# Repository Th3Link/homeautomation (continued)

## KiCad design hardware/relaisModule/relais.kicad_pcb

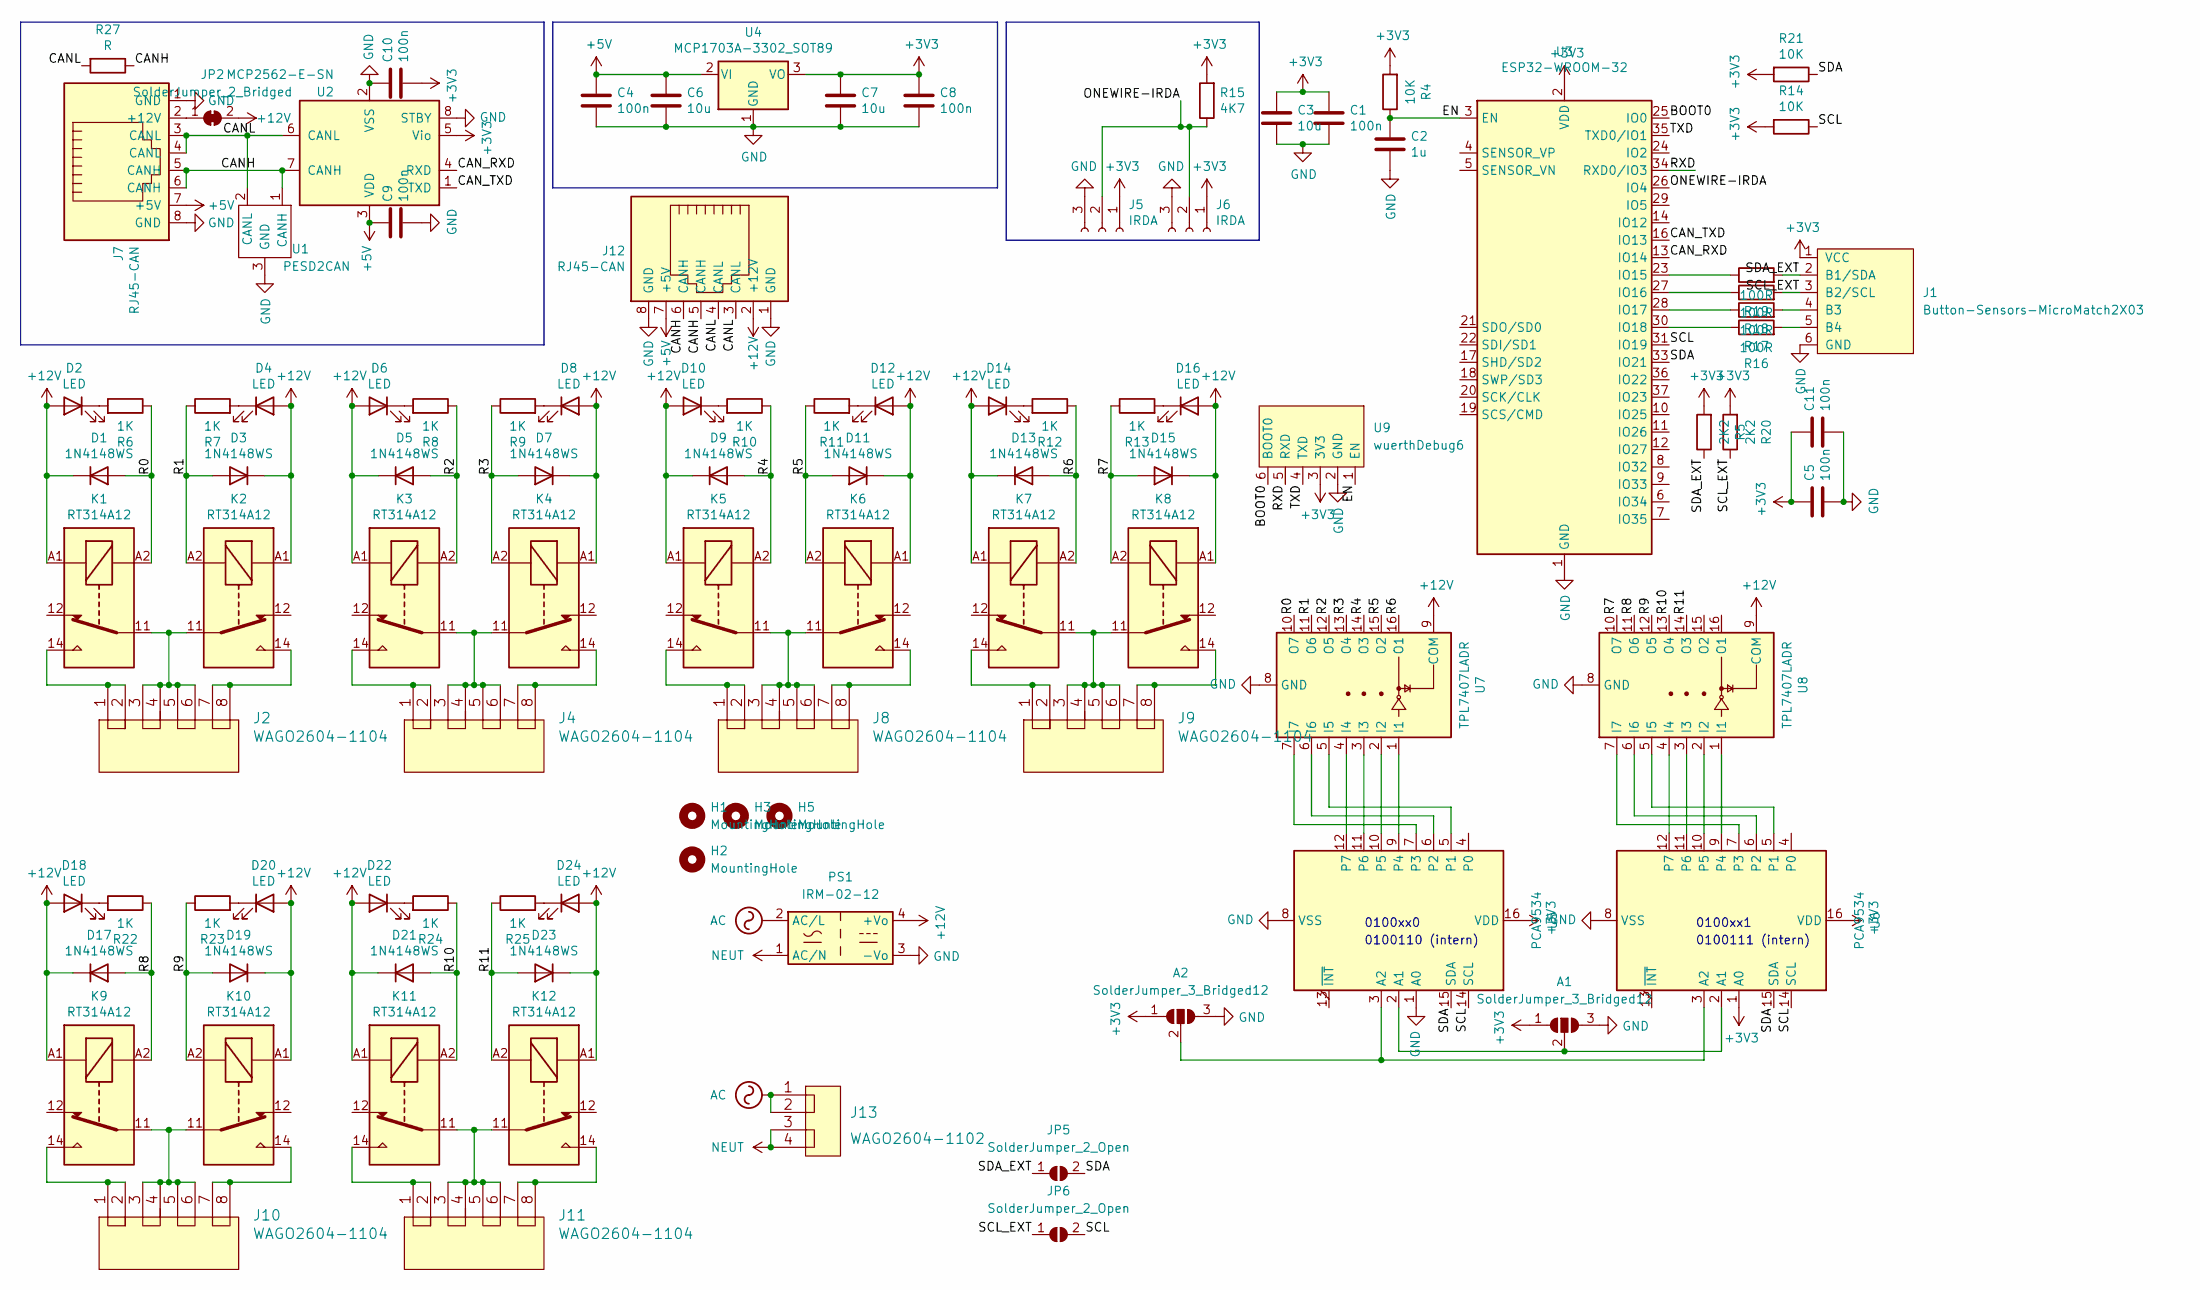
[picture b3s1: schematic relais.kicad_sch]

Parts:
A1, A2: SolderJumper_3_Bridged12; SolderJumper-3_P1.3mm_Open_RoundedPad1.0x1.5mm
C1, C4, C5, C8, C9, C10, C11: 100n; C_0603_1608Metric_Pad1.08x0.95mm_HandSolder
C2: 1u; C_0603_1608Metric_Pad1.08x0.95mm_HandSolder
C3, C6, C7: 10u; C_0805_2012Metric_Pad1.18x1.45mm_HandSolder
D1, D3, D5, D7, D9, D11, D13, D15, D17, D19, D21, D23: 1N4148WS; D_SOD-123
D2, D4, D6, D8, D10, D12, D14, D16, D18, D20, D22, D24: LED; LED_0603_1608Metric_Pad1.05x0.95mm_HandSolder
H1, H2, H3, H5: MountingHole; MountingHole_3.2mm_M3_DIN965
J1: Button-Sensors-MicroMatch2X03; 02x03MicroMatch
J2, J4, J8, J9, J10, J11: WAGO2604-1104
J5, J6: IRDA; PinHeader_1x03_P2.54mm_Vertical
J7, J12: RJ45-CAN; RJ45_OST_PJ012-8P8CX_Vertical
J13: WAGO2604-1102
JP2: SolderJumper_2_Bridged; SolderJumper-2_P1.3mm_Open_RoundedPad1.0x1.5mm
JP5, JP6: SolderJumper_2_Open; SolderJumper-2_P1.3mm_Open_RoundedPad1.0x1.5mm
K1, K2, K3, K4, K5, K6, K7, K8, K9, K10, K11, K12: RT314A12; Relay_SPDT_Schrack-RT1-16A-FormC_RM5mm
PS1: IRM-02-12; Converter_ACDC_MeanWell_IRM-02-xx_THT
R4, R14, R21: 10K; R_0603_1608Metric_Pad0.98x0.95mm_HandSolder
R5, R20: 2K2; R_0603_1608Metric_Pad0.98x0.95mm_HandSolder
R6, R7, R8, R9, R10, R11, R12, R13, R22, R23, R24, R25: 1K; R_0603_1608Metric_Pad0.98x0.95mm_HandSolder
R15: 4K7; R_0603_1608Metric_Pad0.98x0.95mm_HandSolder
R16, R17, R18, R19: 100R; R_0603_1608Metric_Pad0.98x0.95mm_HandSolder
R27: R; R_0603_1608Metric_Pad0.98x0.95mm_HandSolder
U1: PESD2CAN; SOT-23
U2: MCP2562-E-SN; SOIC-8_3.9x4.9mm_P1.27mm
U3: ESP32-WROOM-32
U4: MCP1703A-3302_SOT89; SOT-89-3_Handsoldering
U5, U6: PCA9534; SOIC-16W_7.5x10.3mm_P1.27mm
U7, U8: TPL7407LADR; SO-16_5.3x10.2mm_P1.27mm
U9: wuerthDebug6

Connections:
+3V3: A1.1 (A), A2.1 (A), C1.1, C3.1, C5.1, C7.1, C8.1, C10.1, C11.1, J1.1 (VCC), J5.1, J6.1, R4.2, R5.2, R14.2, R15.2, R20.2, R21.2, U2.5 (Vio), U3.2 (VDD), U4.3 (VO), U5.16 (VDD), U6.1 (A0), U6.16 (VDD), U9.3 (3V3)
+5V: C4.1, C6.1, C9.1, J7.7 (+5V), J12.7 (+5V), U2.3 (VDD), U4.2 (VI)
+12V: D1.1 (K), D2.2 (A), D3.1 (K), D4.2 (A), D5.1 (K), D6.2 (A), D7.1 (K), D8.2 (A), D9.1 (K), D10.2 (A), D11.1 (K), D12.2 (A), D13.1 (K), D14.2 (A), D15.1 (K), D16.2 (A), D17.1 (K), D18.2 (A), D19.1 (K), D20.2 (A), D21.1 (K), D22.2 (A), D23.1 (K), D24.2 (A), J12.2 (+12V), JP2.2 (B), K1.A1, K2.A1, K3.A1, K4.A1, K5.A1, K6.A1, K7.A1, K8.A1, K9.A1, K10.A1, K11.A1, K12.A1, PS1.4 (+Vo), U7.9 (COM), U8.9 (COM)
/BOOT0: U3.25 (IO0), U9.6 (BOOT0)
/CANH: J7.5 (CANH), J7.6 (CANH), J12.5 (CANH), J12.6 (CANH), R27.1, U1.1 (CANH), U2.7 (CANH)
/CANL: J7.3 (CANL), J7.4 (CANL), J12.3 (CANL), J12.4 (CANL), R27.2, U1.2 (CANL), U2.6 (CANL)
/CAN_RXD: U2.4 (RXD), U3.13 (IO14)
/CAN_TXD: U2.1 (TXD), U3.16 (IO13)
/EN: C2.1, R4.1, U3.3 (EN), U9.1 (EN)
/ONEWIRE-IRDA: J5.2, J6.2, R15.1, U3.26 (IO4)
/R0: D1.2 (A), K1.A2, R6.1, U7.10 (O7)
/R1: D3.2 (A), K2.A2, R7.1, U7.11 (O6)
/R2: D5.2 (A), K3.A2, R8.1, U7.12 (O5)
/R3: D7.2 (A), K4.A2, R9.1, U7.13 (O4)
/R4: D9.2 (A), K5.A2, R10.1, U7.14 (O3)
/R5: D11.2 (A), K6.A2, R11.1, U7.15 (O2)
/R6: D13.2 (A), K7.A2, R12.1, U7.16 (O1)
/R7: D15.2 (A), K8.A2, R13.1, U8.10 (O7)
/R8: D17.2 (A), K9.A2, R22.1, U8.11 (O6)
/R9: D19.2 (A), K10.A2, R23.1, U8.12 (O5)
/R10: D21.2 (A), K11.A2, R24.1, U8.13 (O4)
/R11: D23.2 (A), K12.A2, R25.1, U8.14 (O3)
/RXD: U3.34 (RXD0/IO3), U9.5 (RXD)
/SCL: JP6.2 (B), R14.1, U3.31 (IO19), U5.14 (SCL), U6.14 (SCL)
/SCL_EXT: J1.3 (B2/SCL), JP6.1 (A), R18.2, R20.1
/SDA: JP5.2 (B), R21.1, U3.33 (IO21), U5.15 (SDA), U6.15 (SDA)
/SDA_EXT: J1.2 (B1/SDA), JP5.1 (A), R5.1, R19.2
/TXD: U3.35 (TXD0/IO1), U9.4 (TXD)
AC: J13.1, J13.2, PS1.2 (AC/L)
GND: A1.3 (B), A2.3 (B), C1.2, C2.2, C3.2, C4.2, C5.2, C6.2, C7.2, C8.2, C9.2, C10.2, C11.2, J1.6 (GND), J5.3, J6.3, J7.1 (GND), J7.8 (GND), J12.1 (GND), J12.8 (GND), PS1.3 (-Vo), U1.3 (GND), U2.2 (VSS), U2.8 (STBY), U3.1 (GND), U3.15 (GND), U3.38 (GND), U3.39 (GND), U4.1 (GND), U5.1 (A0), U5.8 (VSS), U6.8 (VSS), U7.8 (GND), U8.8 (GND), U9.2 (GND)
NEUT: J13.3, J13.4, PS1.1 (AC/N)
unnamed: A1.2 (C), U5.2 (A1), U6.2 (A1)
unnamed: A2.2 (C), U5.3 (A2), U6.3 (A2)
unnamed: D2.1 (K), R6.2
unnamed: D4.1 (K), R7.2
unnamed: D6.1 (K), R8.2
unnamed: D8.1 (K), R9.2
unnamed: D10.1 (K), R10.2
unnamed: D12.1 (K), R11.2
unnamed: D14.1 (K), R12.2
unnamed: D16.1 (K), R13.2
unnamed: D18.1 (K), R22.2
unnamed: D20.1 (K), R23.2
unnamed: D22.1 (K), R24.2
unnamed: D24.1 (K), R25.2
unnamed: J1.4 (B3), R17.2
unnamed: J1.5 (B4), R16.2
unnamed: J2.1, J2.2, K1.14
unnamed: J2.3, J2.4, J2.5, J2.6, K1.11, K2.11
unnamed: J2.7, J2.8, K2.14
unnamed: J4.1, J4.2, K3.14
unnamed: J4.3, J4.4, J4.5, J4.6, K3.11, K4.11
unnamed: J4.7, J4.8, K4.14
unnamed: J7.2 (+12V), JP2.1 (A)
unnamed: J8.1, J8.2, K5.14
unnamed: J8.3, J8.4, J8.5, J8.6, K5.11, K6.11
unnamed: J8.7, J8.8, K6.14
unnamed: J9.1, J9.2, K7.14
unnamed: J9.3, J9.4, J9.5, J9.6, K7.11, K8.11
unnamed: J9.7, J9.8, K8.14
unnamed: J10.1, J10.2, K9.14
unnamed: J10.3, J10.4, J10.5, J10.6, K9.11, K10.11
unnamed: J10.7, J10.8, K10.14
unnamed: J11.1, J11.2, K11.14
unnamed: J11.3, J11.4, J11.5, J11.6, K11.11, K12.11
unnamed: J11.7, J11.8, K12.14
unnamed: R16.1, U3.30 (IO18)
unnamed: R17.1, U3.28 (IO17)
unnamed: R18.1, U3.27 (IO16)
unnamed: R19.1, U3.23 (IO15)
unnamed: U5.5 (P1), U7.5 (I5)
unnamed: U5.6 (P2), U7.6 (I6)
unnamed: U5.7 (P3), U7.7 (I7)
unnamed: U5.9 (P4), U7.1 (I1)
unnamed: U5.10 (P5), U7.2 (I2)
unnamed: U5.11 (P6), U7.3 (I3)
unnamed: U5.12 (P7), U7.4 (I4)
unnamed: U6.5 (P1), U8.5 (I5)
unnamed: U6.6 (P2), U8.6 (I6)
unnamed: U6.7 (P3), U8.7 (I7)
unnamed: U6.9 (P4), U8.1 (I1)
unnamed: U6.10 (P5), U8.2 (I2)
unnamed: U6.11 (P6), U8.3 (I3)
unnamed: U6.12 (P7), U8.4 (I4)

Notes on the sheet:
0100110 (intern)
0100111 (intern)
0100xx0
0100xx1

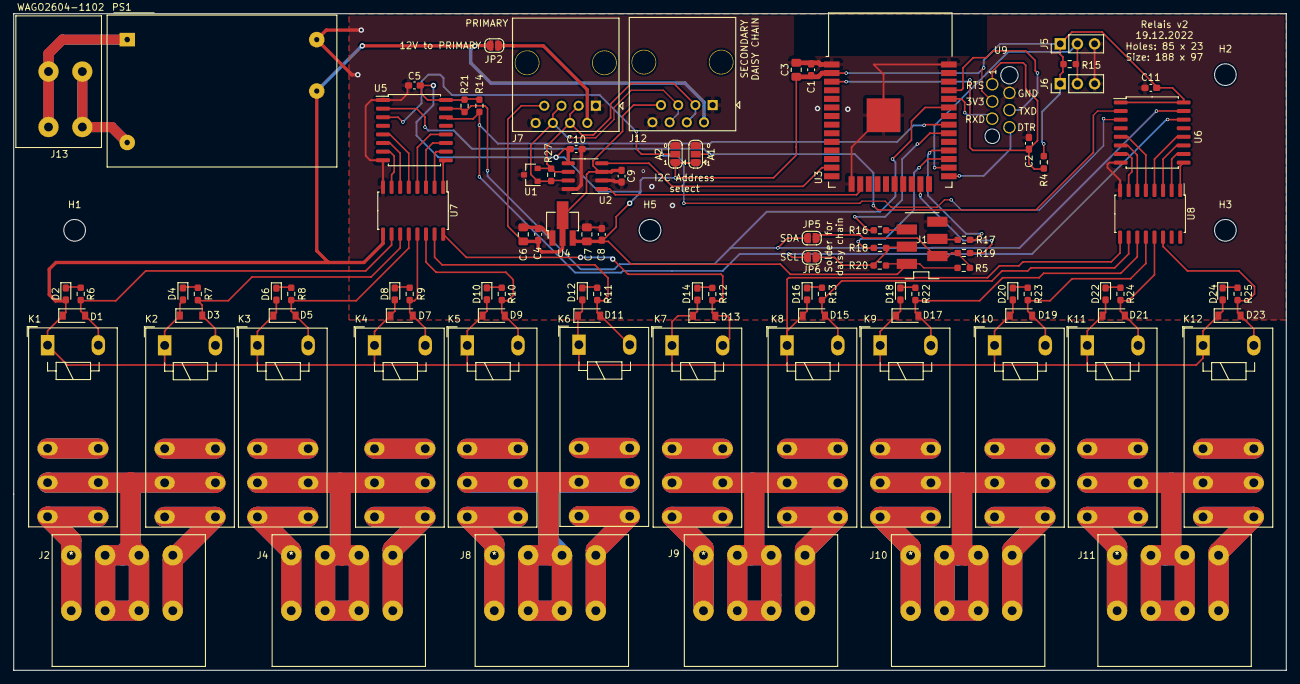
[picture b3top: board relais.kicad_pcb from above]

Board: 2 copper layers, 188.0 x 97.0 mm, 101 parts (0 on the bottom side), 84 nets.

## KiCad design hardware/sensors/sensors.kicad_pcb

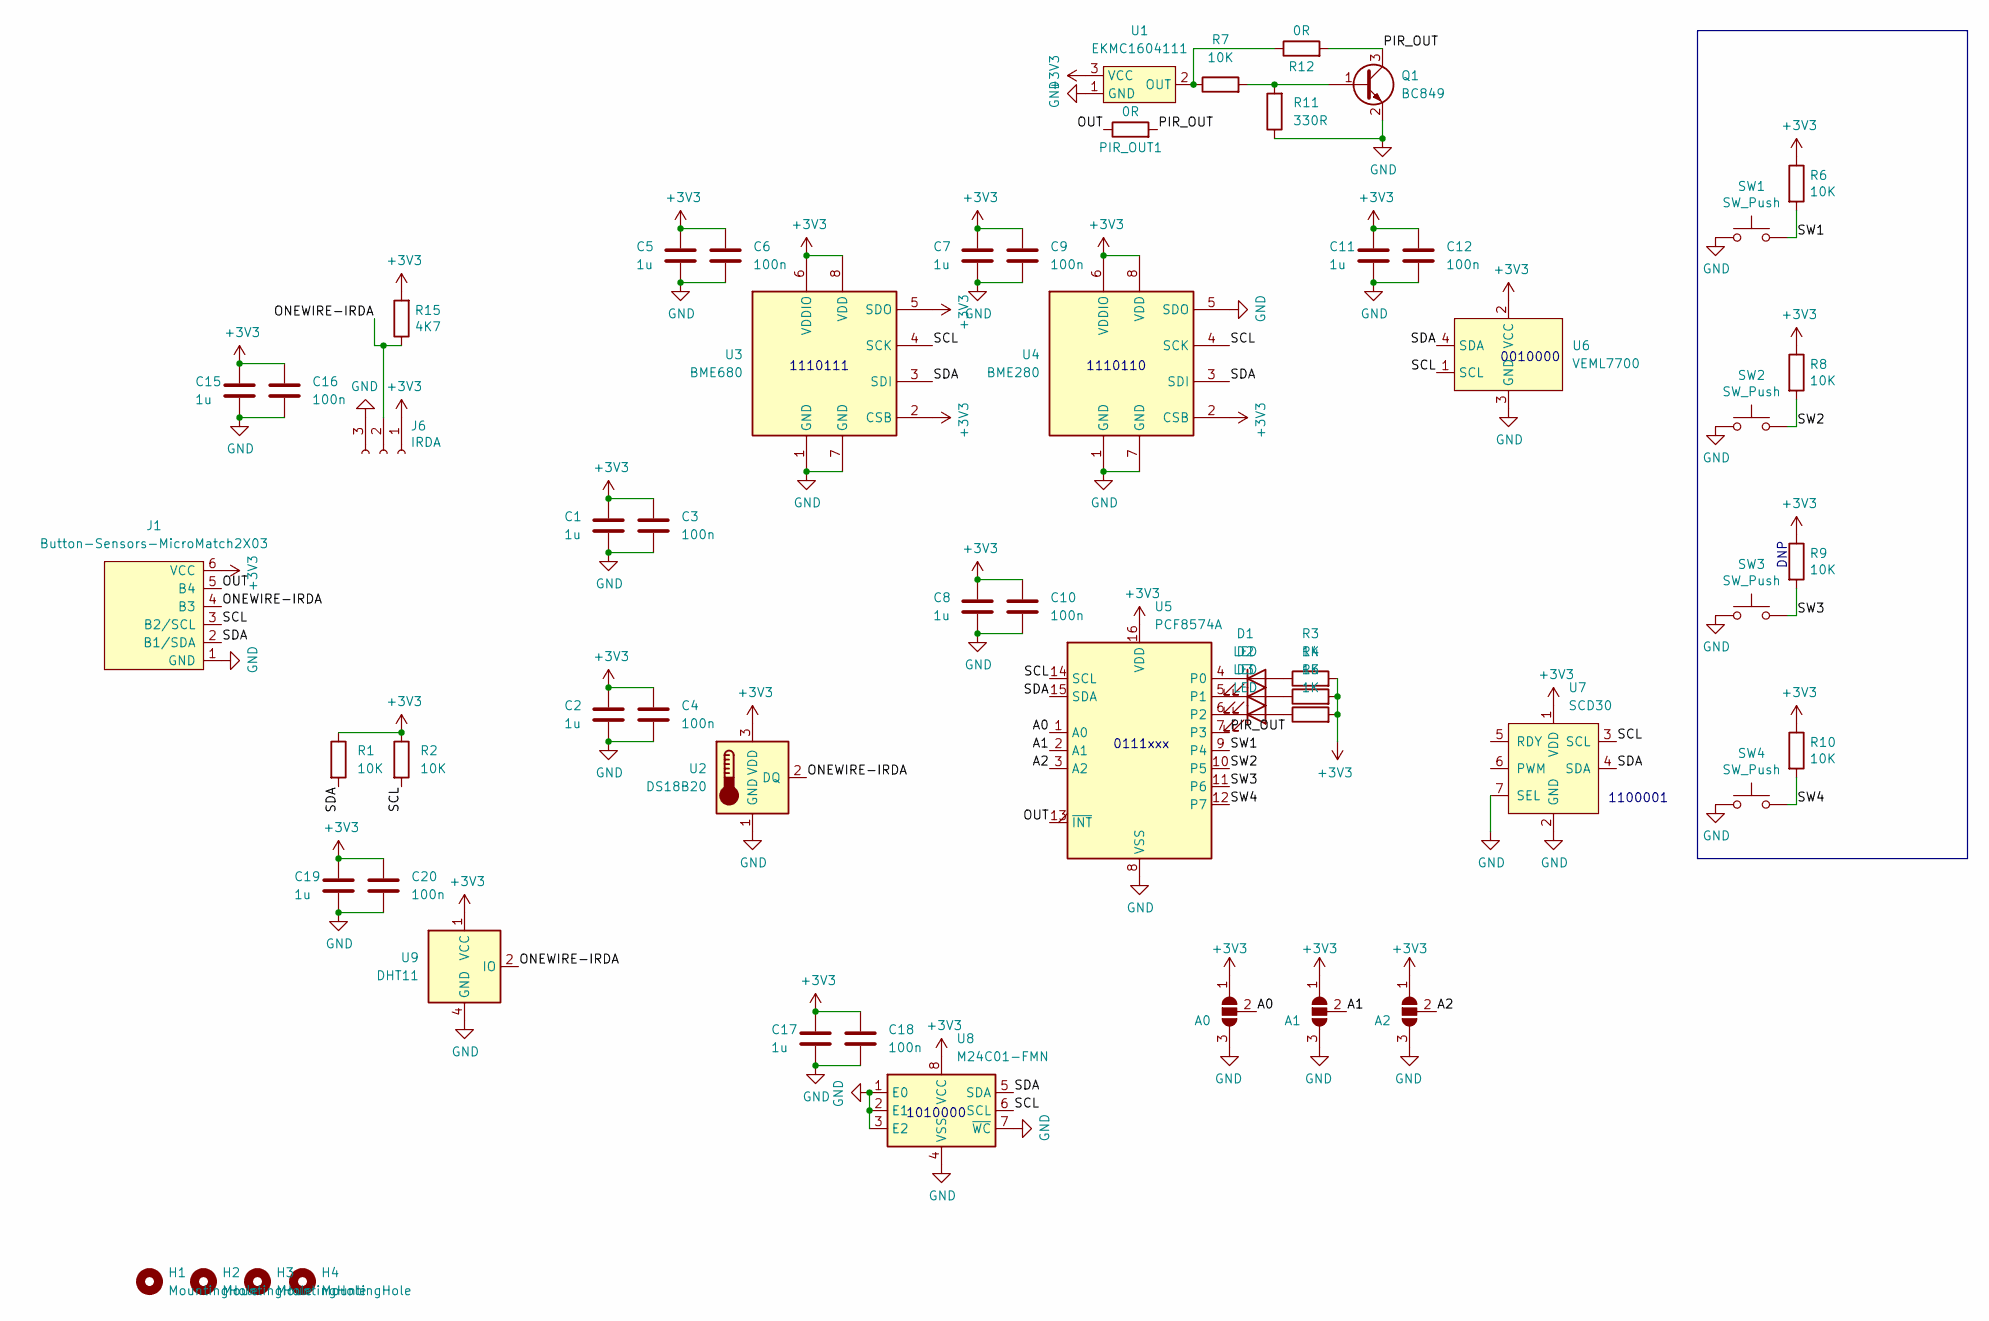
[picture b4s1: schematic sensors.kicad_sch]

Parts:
A0, A1, A2: SolderJumper_3_Open; SolderJumper-3_P1.3mm_Open_RoundedPad1.0x1.5mm
C1, C2, C5, C7, C8, C11, C15, C17, C19: 1u; C_0603_1608Metric_Pad1.08x0.95mm_HandSolder
C3, C4, C6, C9, C10, C12, C16, C18, C20: 100n; C_0603_1608Metric_Pad1.08x0.95mm_HandSolder
D1, D2, D3: LED; LED_0805_2012Metric_Pad1.15x1.40mm_HandSolder
H1, H2, H3, H4: MountingHole; MountingHole_2.2mm_M2
J1: Button-Sensors-MicroMatch2X03; 02x03MicroMatch
J6: IRDA; PinHeader_1x03_P2.54mm_Vertical
PIR_OUT1: 0R; SolderJumper-2_P1.3mm_Open_RoundedPad1.0x1.5mm
Q1: BC849; SOT-23
R1, R2, R6, R7, R8, R9, R10: 10K; R_0603_1608Metric_Pad0.98x0.95mm_HandSolder
R3, R4, R5: 1K; R_0603_1608Metric_Pad0.98x0.95mm_HandSolder
R11: 330R; R_0603_1608Metric_Pad0.98x0.95mm_HandSolder
R12: 0R; SolderJumper-2_P1.3mm_Open_RoundedPad1.0x1.5mm
R15: 4K7; R_0603_1608Metric_Pad0.98x0.95mm_HandSolder
SW1, SW2, SW3, SW4: SW_Push; SW_SPST_TL3305A
U1: EKMC1604111
U2: DS18B20; TO-92_Inline
U3: BME680; Bosch_LGA-8
U4: BME280; Bosch_LGA-8
U5: PCF8574A; SOIC-16W_7.5x10.3mm_P1.27mm
U6: VEML7700
U7: SCD30
U8: M24C01-FMN; SOIC-8_3.9x4.9mm_P1.27mm
U9: DHT11; Aosong_DHT11_5.5x12.0_P2.54mm

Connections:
+3V3: A0.1 (A), A1.1 (A), A2.1 (A), C1.1, C2.1, C3.1, C4.1, C5.1, C6.1, C7.1, C8.1, C9.1, C10.1, C11.1, C12.1, C15.1, C16.1, C17.1, C18.1, C19.1, C20.1, J1.6 (VCC), J6.1, R1.1, R2.1, R3.2, R4.2, R5.2, R6.1, R8.1, R9.1, R10.1, R15.2, U1.3 (VCC), U2.3 (VDD), U3.2 (CSB), U3.5 (SDO), U3.6 (VDDIO), U3.8 (VDD), U4.2 (CSB), U4.6 (VDDIO), U4.8 (VDD), U5.16 (VDD), U6.2 (VCC), U7.1 (VDD), U8.8 (VCC), U9.1 (VCC)
/A0: A0.2 (C), U5.1 (A0)
/A1: A1.2 (C), U5.2 (A1)
/A2: A2.2 (C), U5.3 (A2)
/ONEWIRE-IRDA: J1.4 (B3), J6.2, R15.1, U2.2 (DQ), U9.2 (IO)
/OUT: J1.5 (B4), PIR_OUT1.1, U5.13 (~INT)
/PIR_OUT: PIR_OUT1.2, Q1.3 (C), R12.2, U5.7 (P3)
/SCL: J1.3 (B2/SCL), R2.2, U3.4 (SCK), U4.4 (SCK), U5.14 (SCL), U6.1 (SCL), U7.3 (SCL), U8.6 (SCL)
/SDA: J1.2 (B1/SDA), R1.2, U3.3 (SDI), U4.3 (SDI), U5.15 (SDA), U6.4 (SDA), U7.4 (SDA), U8.5 (SDA)
/SW1: R6.2, SW1.2, U5.9 (P4)
/SW2: R8.2, SW2.2, U5.10 (P5)
/SW3: R9.2, SW3.2, U5.11 (P6)
/SW4: R10.2, SW4.2, U5.12 (P7)
GND: A0.3 (B), A1.3 (B), A2.3 (B), C1.2, C2.2, C3.2, C4.2, C5.2, C6.2, C7.2, C8.2, C9.2, C10.2, C11.2, C12.2, C15.2, C16.2, C17.2, C18.2, C19.2, C20.2, J1.1 (GND), J6.3, Q1.2 (E), R11.1, SW1.1, SW2.1, SW3.1, SW4.1, U1.1 (GND), U2.1 (GND), U3.1 (GND), U3.7 (GND), U4.1 (GND), U4.5 (SDO), U4.7 (GND), U5.8 (VSS), U6.3 (GND), U7.2 (GND), U7.7 (SEL), U8.1 (E0), U8.2 (E1), U8.3 (E2), U8.4 (VSS), U8.7 (~WC), U9.4 (GND)
unnamed: D1.1 (K), U5.4 (P0)
unnamed: D1.2 (A), R3.1
unnamed: D2.1 (K), U5.5 (P1)
unnamed: D2.2 (A), R4.1
unnamed: D3.1 (K), U5.6 (P2)
unnamed: D3.2 (A), R5.1
unnamed: Q1.1 (B), R7.2, R11.2
unnamed: R7.1, R12.1, U1.2 (OUT)

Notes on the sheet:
0111xxx
1100001
1110110
DNP
1010000
0010000
1110111

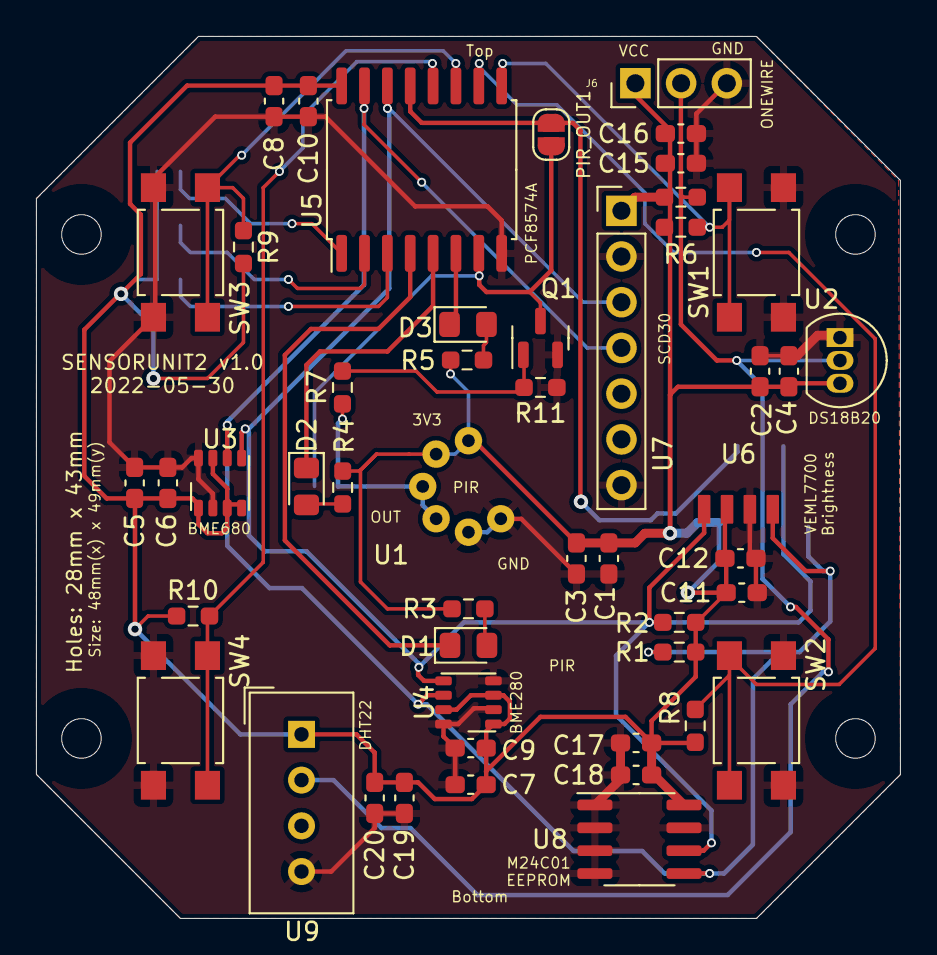
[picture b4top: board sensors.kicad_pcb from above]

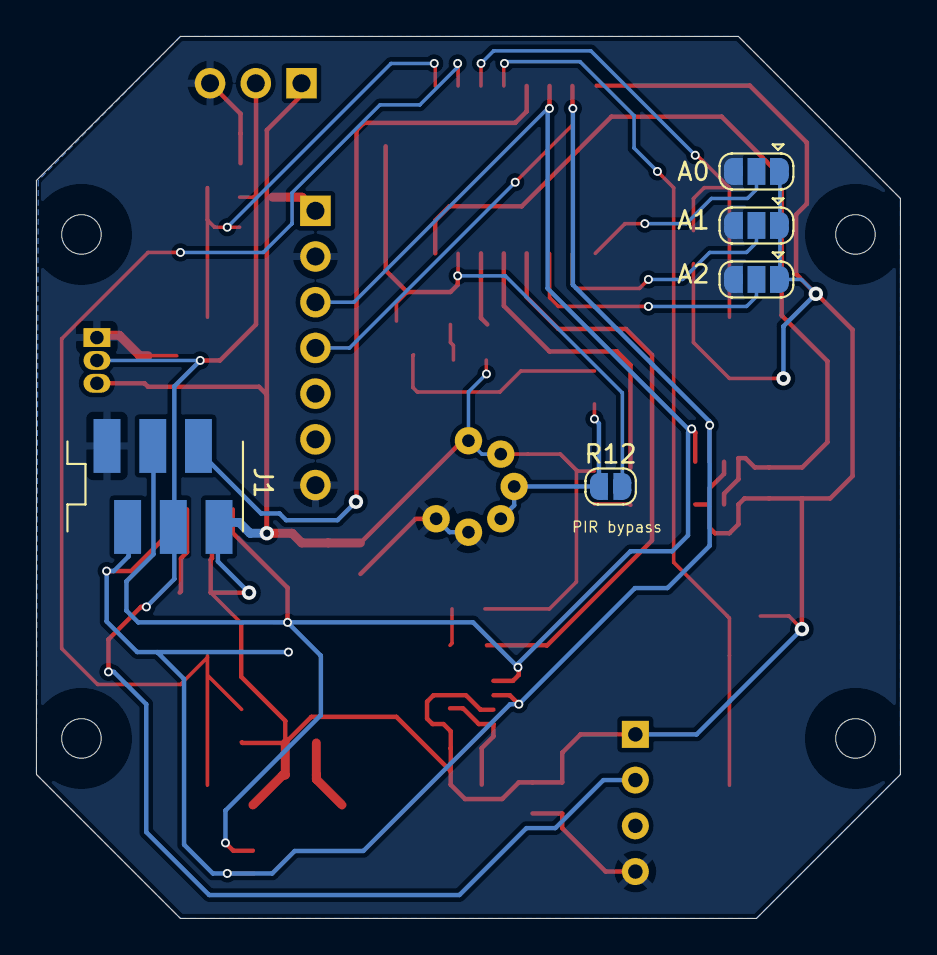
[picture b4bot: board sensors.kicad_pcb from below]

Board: 2 copper layers, 48.0 x 49.0 mm, 58 parts (5 on the bottom side), 22 nets.

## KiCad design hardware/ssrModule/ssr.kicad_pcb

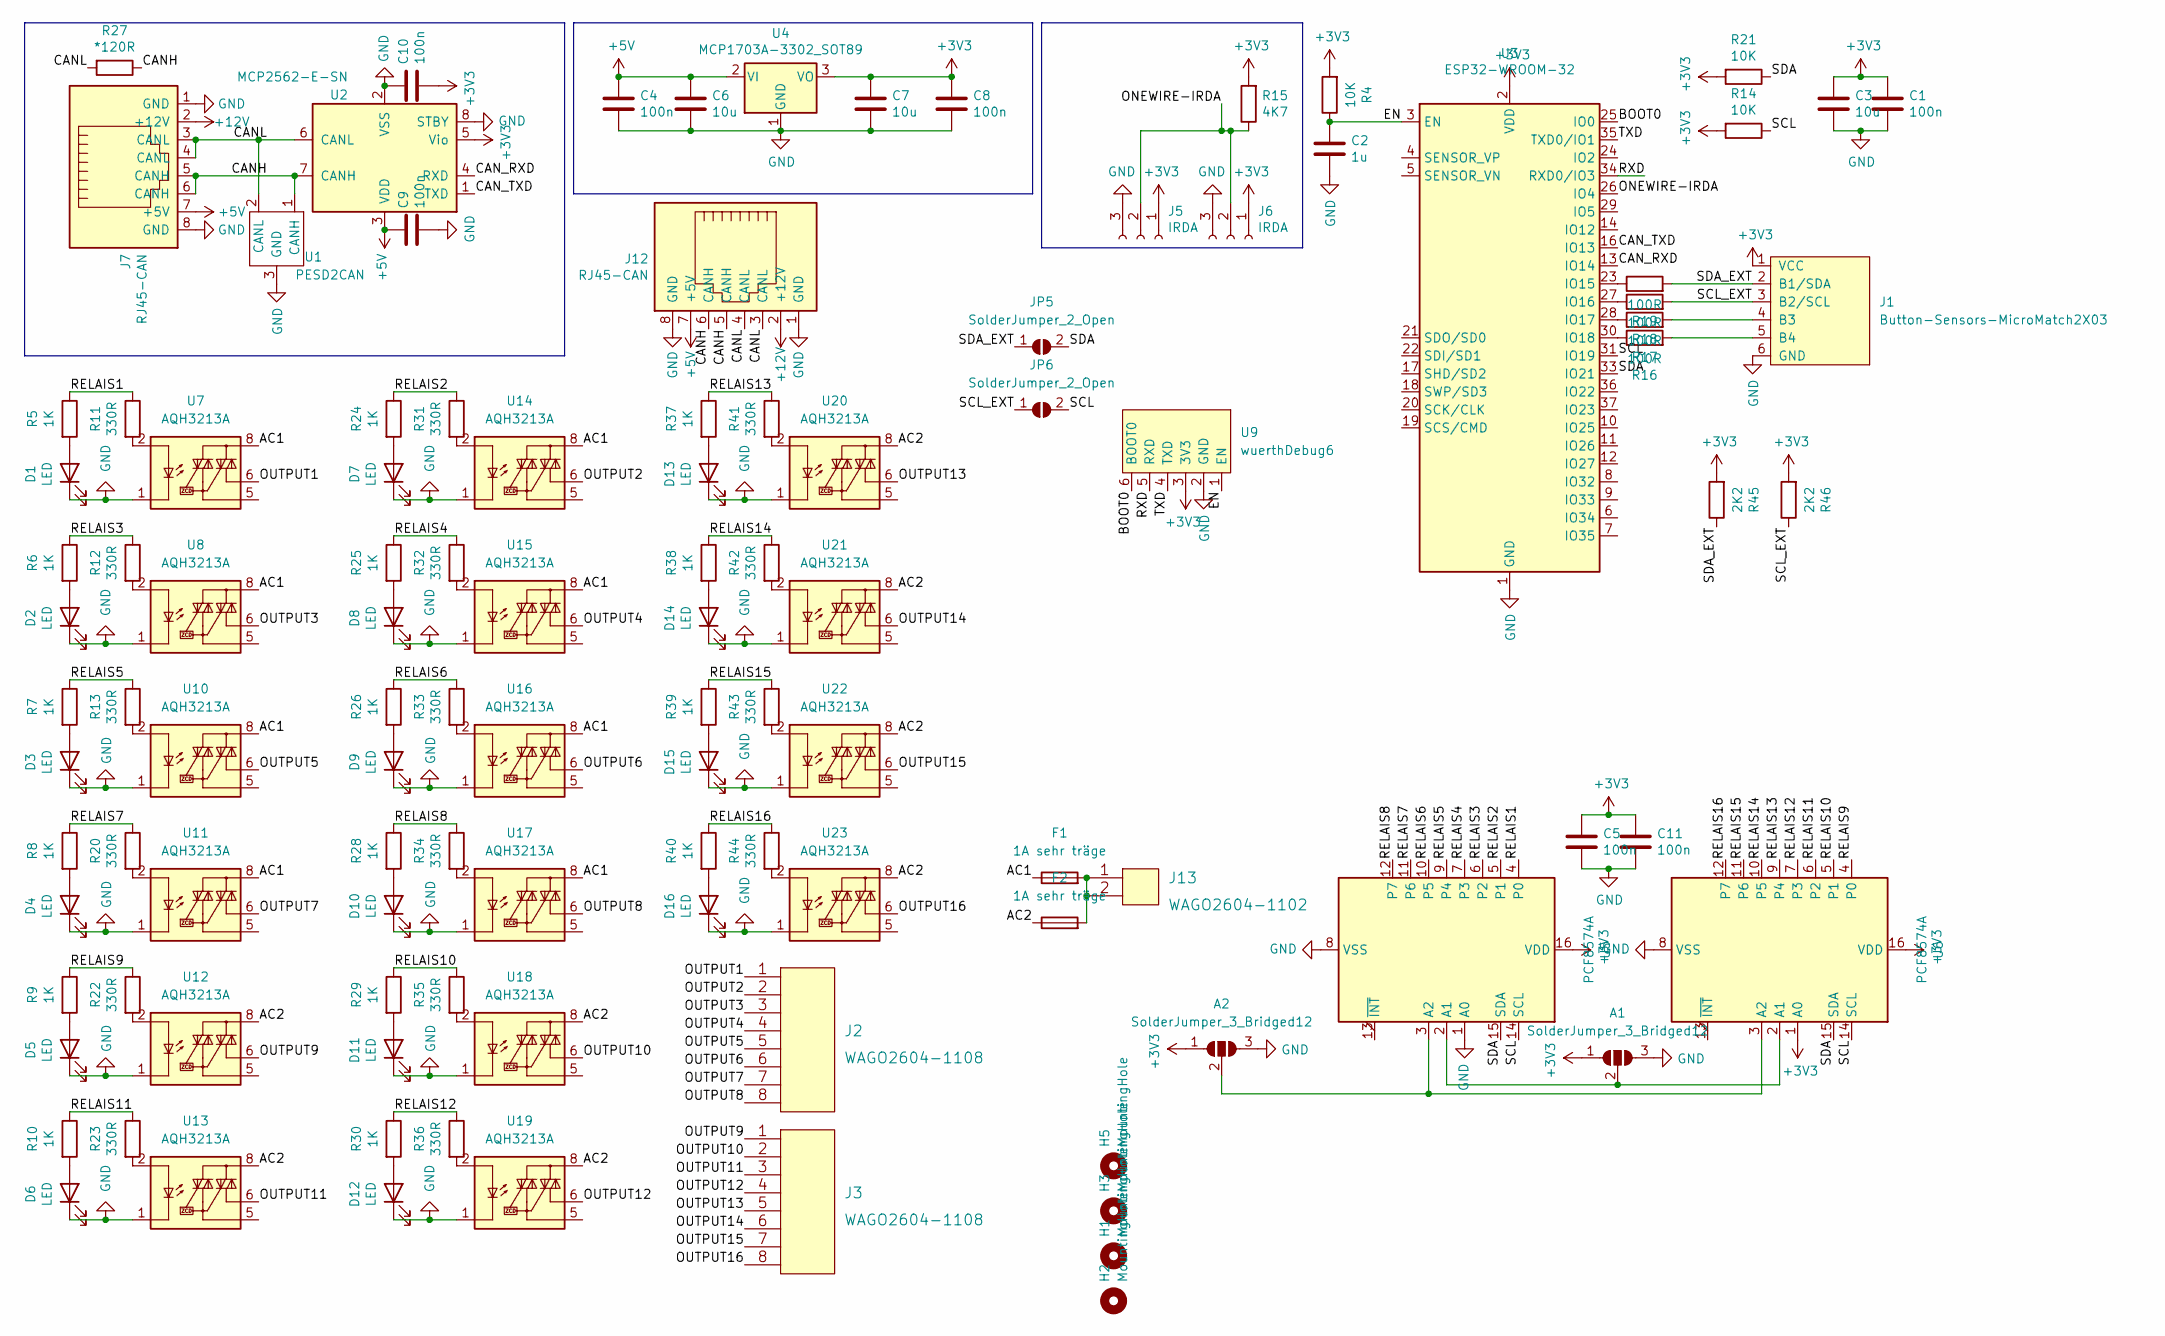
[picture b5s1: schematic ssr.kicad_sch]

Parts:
A1, A2: SolderJumper_3_Bridged12; SolderJumper-3_P1.3mm_Open_RoundedPad1.0x1.5mm
C1, C4, C5, C8, C9, C10, C11: 100n; C_0603_1608Metric_Pad1.08x0.95mm_HandSolder
C2: 1u; C_0603_1608Metric_Pad1.08x0.95mm_HandSolder
C3, C6, C7: 10u; C_0805_2012Metric_Pad1.18x1.45mm_HandSolder
D1, D2, D3, D4, D5, D6, D7, D8, D9, D10, D11, D12, D13, D14, D15, D16: LED; LED_0603_1608Metric_Pad1.05x0.95mm_HandSolder
F1, F2: 1A sehr träge; Fuseholder_Cylinder-5x20mm_Schurter_0031_8201_Horizontal_Op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
H1, H2, H3, H5: MountingHole; MountingHole_3.2mm_M3_DIN965
J1: Button-Sensors-MicroMatch2X03; 02x03MicroMatch
J2, J3: WAGO2604-1108
J5, J6: IRDA; PinHeader_1x03_P2.54mm_Vertical
J7, J12: RJ45-CAN; RJ45_OST_PJ012-8P8CX_Vertical
J13: WAGO2604-1102
JP5, JP6: SolderJumper_2_Open; SolderJumper-2_P1.3mm_Open_RoundedPad1.0x1.5mm
R4, R14, R21: 10K; R_0603_1608Metric_Pad0.98x0.95mm_HandSolder
R5, R6, R7, R8, R9, R10, R24, R25, R26, R28, R29, R30, R37, R38, R39, R40: 1K; R_0603_1608Metric_Pad0.98x0.95mm_HandSolder
R11, R12, R13, R20, R22, R23, R31, R32, R33, R34, R35, R36, R41, R42, R43, R44: 330R; R_0603_1608Metric_Pad0.98x0.95mm_HandSolder
R15: 4K7; R_0603_1608Metric_Pad0.98x0.95mm_HandSolder
R16, R17, R18, R19: 100R; R_0603_1608Metric_Pad0.98x0.95mm_HandSolder
R27: *120R; R_0603_1608Metric_Pad0.98x0.95mm_HandSolder
R45, R46: 2K2; R_0603_1608Metric_Pad0.98x0.95mm_HandSolder
U1: PESD2CAN; SOT-23
U2: MCP2562-E-SN; SOIC-8_3.9x4.9mm_P1.27mm
U3: ESP32-WROOM-32
U4: MCP1703A-3302_SOT89; SOT-89-3_Handsoldering
U5, U6: PCF8574A; SOIC-16W_7.5x10.3mm_P1.27mm
U7, U8, U10, U11, U12, U13, U14, U15, U16, U17, U18, U19, U20, U21, U22, U23: AQH3213A; SSO-7-8_6.4x9.78mm_P2.54mm
U9: wuerthDebug6

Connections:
+3V3: A1.1 (A), A2.1 (A), C1.1, C3.1, C5.1, C7.1, C8.1, C10.1, C11.1, J1.1 (VCC), J5.1, J6.1, R4.2, R14.2, R15.2, R21.2, R45.2, R46.2, U2.5 (Vio), U3.2 (VDD), U4.3 (VO), U5.16 (VDD), U6.1 (A0), U6.16 (VDD), U9.3 (3V3)
+5V: C4.1, C6.1, C9.1, J7.7 (+5V), J12.7 (+5V), U2.3 (VDD), U4.2 (VI)
+12V: J7.2 (+12V), J12.2 (+12V)
/AC1: F1.1, U7.8, U8.8, U10.8, U11.8, U14.8, U15.8, U16.8, U17.8
/AC2: F2.1, U12.8, U13.8, U18.8, U19.8, U20.8, U21.8, U22.8, U23.8
/BOOT0: U3.25 (IO0), U9.6 (BOOT0)
/CANH: J7.5 (CANH), J7.6 (CANH), J12.5 (CANH), J12.6 (CANH), R27.1, U1.1 (CANH), U2.7 (CANH)
/CANL: J7.3 (CANL), J7.4 (CANL), J12.3 (CANL), J12.4 (CANL), R27.2, U1.2 (CANL), U2.6 (CANL)
/CAN_RXD: U2.4 (RXD), U3.13 (IO14)
/CAN_TXD: U2.1 (TXD), U3.16 (IO13)
/EN: C2.1, R4.1, U3.3 (EN), U9.1 (EN)
/ONEWIRE-IRDA: J5.2, J6.2, R15.1, U3.26 (IO4)
/OUTPUT1: J2.1, U7.6
/OUTPUT2: J2.2, U14.6
/OUTPUT3: J2.3, U8.6
/OUTPUT4: J2.4, U15.6
/OUTPUT5: J2.5, U10.6
/OUTPUT6: J2.6, U16.6
/OUTPUT7: J2.7, U11.6
/OUTPUT8: J2.8, U17.6
/OUTPUT9: J3.1, U12.6
/OUTPUT10: J3.2, U18.6
/OUTPUT11: J3.3, U13.6
/OUTPUT12: J3.4, U19.6
/OUTPUT13: J3.5, U20.6
/OUTPUT14: J3.6, U21.6
/OUTPUT15: J3.7, U22.6
/OUTPUT16: J3.8, U23.6
/RELAIS1: R5.1, R11.1, U5.4 (P0)
/RELAIS2: R24.1, R31.1, U5.5 (P1)
/RELAIS3: R6.1, R12.1, U5.6 (P2)
/RELAIS4: R25.1, R32.1, U5.7 (P3)
/RELAIS5: R7.1, R13.1, U5.9 (P4)
/RELAIS6: R26.1, R33.1, U5.10 (P5)
/RELAIS7: R8.1, R20.1, U5.11 (P6)
/RELAIS8: R28.1, R34.1, U5.12 (P7)
/RELAIS9: R9.1, R22.1, U6.4 (P0)
/RELAIS10: R29.1, R35.1, U6.5 (P1)
/RELAIS11: R10.1, R23.1, U6.6 (P2)
/RELAIS12: R30.1, R36.1, U6.7 (P3)
/RELAIS13: R37.1, R41.1, U6.9 (P4)
/RELAIS14: R38.1, R42.1, U6.10 (P5)
/RELAIS15: R39.1, R43.1, U6.11 (P6)
/RELAIS16: R40.1, R44.1, U6.12 (P7)
/RXD: U3.34 (RXD0/IO3), U9.5 (RXD)
/SCL: JP6.2 (B), R14.1, U3.31 (IO19), U5.14 (SCL), U6.14 (SCL)
/SCL_EXT: J1.3 (B2/SCL), JP6.1 (A), R18.2, R46.1
/SDA: JP5.2 (B), R21.1, U3.33 (IO21), U5.15 (SDA), U6.15 (SDA)
/SDA_EXT: J1.2 (B1/SDA), JP5.1 (A), R19.2, R45.1
/TXD: U3.35 (TXD0/IO1), U9.4 (TXD)
GND: A1.3 (B), A2.3 (B), C1.2, C2.2, C3.2, C4.2, C5.2, C6.2, C7.2, C8.2, C9.2, C10.2, C11.2, D1.1 (K), D2.1 (K), D3.1 (K), D4.1 (K), D5.1 (K), D6.1 (K), D7.1 (K), D8.1 (K), D9.1 (K), D10.1 (K), D11.1 (K), D12.1 (K), D13.1 (K), D14.1 (K), D15.1 (K), D16.1 (K), J1.6 (GND), J5.3, J6.3, J7.1 (GND), J7.8 (GND), J12.1 (GND), J12.8 (GND), U1.3 (GND), U2.2 (VSS), U2.8 (STBY), U3.1 (GND), U3.15 (GND), U3.38 (GND), U3.39 (GND), U4.1 (GND), U5.1 (A0), U5.8 (VSS), U6.8 (VSS), U7.1, U7.3, U7.4, U8.1, U8.3, U8.4, U9.2 (GND), U10.1, U10.3, U10.4, U11.1, U11.3, U11.4, U12.1, U12.3, U12.4, U13.1, U13.3, U13.4, U14.1, U14.3, U14.4, U15.1, U15.3, U15.4, U16.1, U16.3, U16.4, U17.1, U17.3, U17.4, U18.1, U18.3, U18.4, U19.1, U19.3, U19.4, U20.1, U20.3, U20.4, U21.1, U21.3, U21.4, U22.1, U22.3, U22.4, U23.1, U23.3, U23.4
unnamed: A1.2 (C), U5.2 (A1), U6.2 (A1)
unnamed: A2.2 (C), U5.3 (A2), U6.3 (A2)
unnamed: D1.2 (A), R5.2
unnamed: D2.2 (A), R6.2
unnamed: D3.2 (A), R7.2
unnamed: D4.2 (A), R8.2
unnamed: D5.2 (A), R9.2
unnamed: D6.2 (A), R10.2
unnamed: D7.2 (A), R24.2
unnamed: D8.2 (A), R25.2
unnamed: D9.2 (A), R26.2
unnamed: D10.2 (A), R28.2
unnamed: D11.2 (A), R29.2
unnamed: D12.2 (A), R30.2
unnamed: D13.2 (A), R37.2
unnamed: D14.2 (A), R38.2
unnamed: D15.2 (A), R39.2
unnamed: D16.2 (A), R40.2
unnamed: F1.2, F2.2, J13.1, J13.2
unnamed: J1.4 (B3), R17.2
unnamed: J1.5 (B4), R16.2
unnamed: R11.2, U7.2
unnamed: R12.2, U8.2
unnamed: R13.2, U10.2
unnamed: R16.1, U3.30 (IO18)
unnamed: R17.1, U3.28 (IO17)
unnamed: R18.1, U3.27 (IO16)
unnamed: R19.1, U3.23 (IO15)
unnamed: R20.2, U11.2
unnamed: R22.2, U12.2
unnamed: R23.2, U13.2
unnamed: R31.2, U14.2
unnamed: R32.2, U15.2
unnamed: R33.2, U16.2
unnamed: R34.2, U17.2
unnamed: R35.2, U18.2
unnamed: R36.2, U19.2
unnamed: R41.2, U20.2
unnamed: R42.2, U21.2
unnamed: R43.2, U22.2
unnamed: R44.2, U23.2

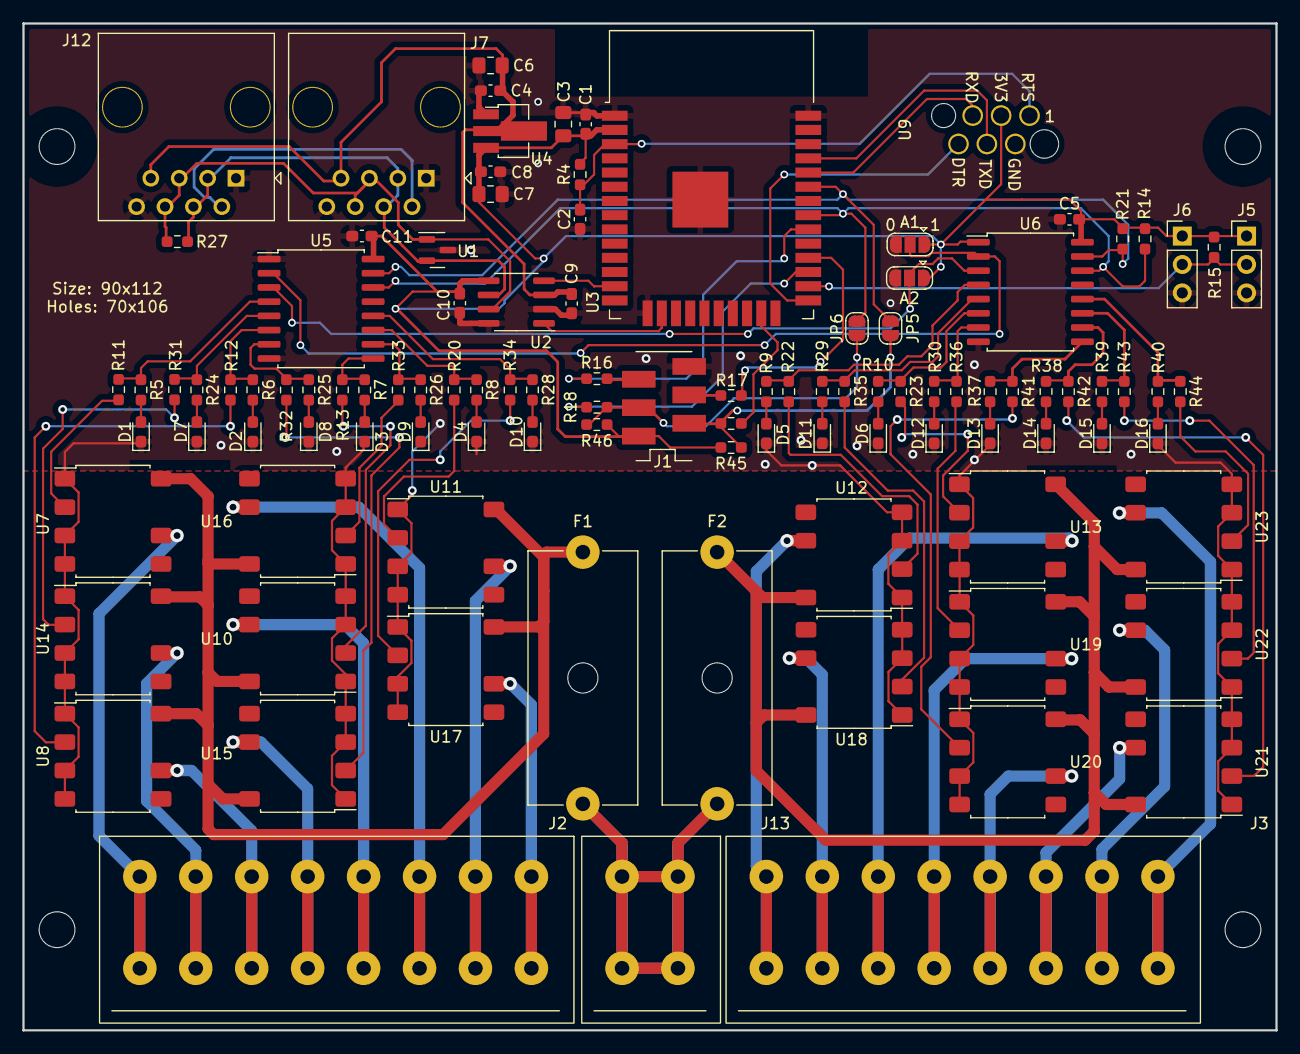
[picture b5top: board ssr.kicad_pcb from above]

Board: 2 copper layers, 112.0 x 90.0 mm, 111 parts (0 on the bottom side), 92 nets.
